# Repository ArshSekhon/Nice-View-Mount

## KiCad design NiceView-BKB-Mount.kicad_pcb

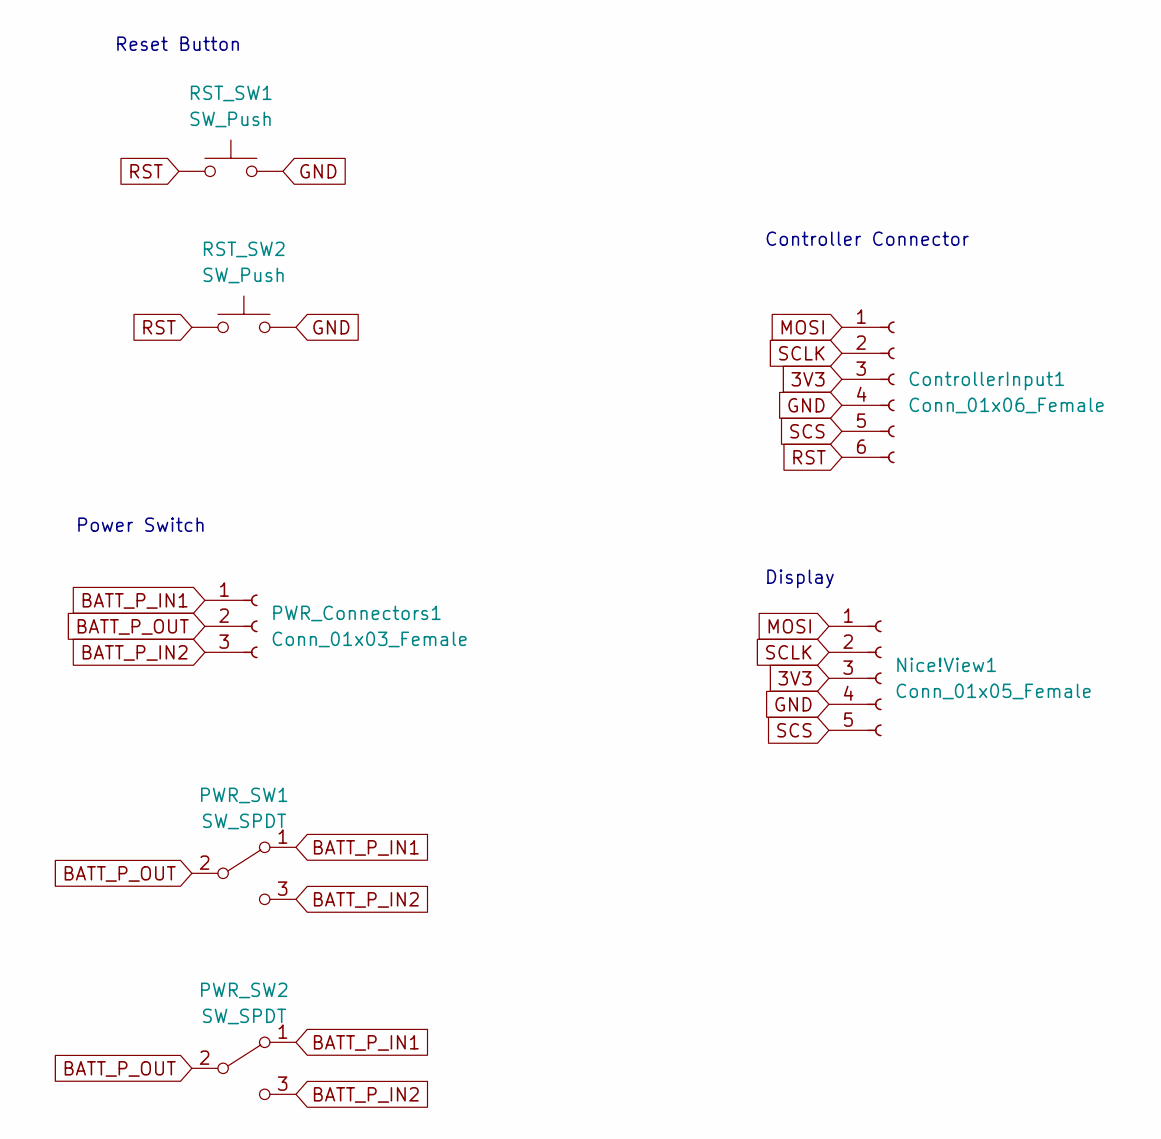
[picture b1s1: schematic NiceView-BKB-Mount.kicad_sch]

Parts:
ControllerInput1: Conn_01x06_Female; PinHeader_1x06_P2.54mm_Vertical
Nice!View1: Conn_01x05_Female; NiceView
PWR_Connectors1: Conn_01x03_Female; PinHeader_1x03_P2.54mm_Vertical
PWR_SW1, PWR_SW2: SW_SPDT; SW_SS12D07VG4
RST_SW1, RST_SW2: SW_Push; PushSwitch

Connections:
3V3: ControllerInput1.3, Nice!View1.3
BATT_P_IN1: PWR_Connectors1.1, PWR_SW1.1 (A), PWR_SW2.1 (A)
BATT_P_IN2: PWR_Connectors1.3, PWR_SW1.3 (C), PWR_SW2.3 (C)
BATT_P_OUT: PWR_Connectors1.2, PWR_SW1.2 (B), PWR_SW2.2 (B)
GND: ControllerInput1.4, Nice!View1.4, RST_SW1.2, RST_SW2.2
MOSI: ControllerInput1.1, Nice!View1.1
RST: ControllerInput1.6, RST_SW1.1, RST_SW2.1
SCLK: ControllerInput1.2, Nice!View1.2
SCS: ControllerInput1.5, Nice!View1.5

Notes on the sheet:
Reset Button
Controller Connector
Power Switch
Display

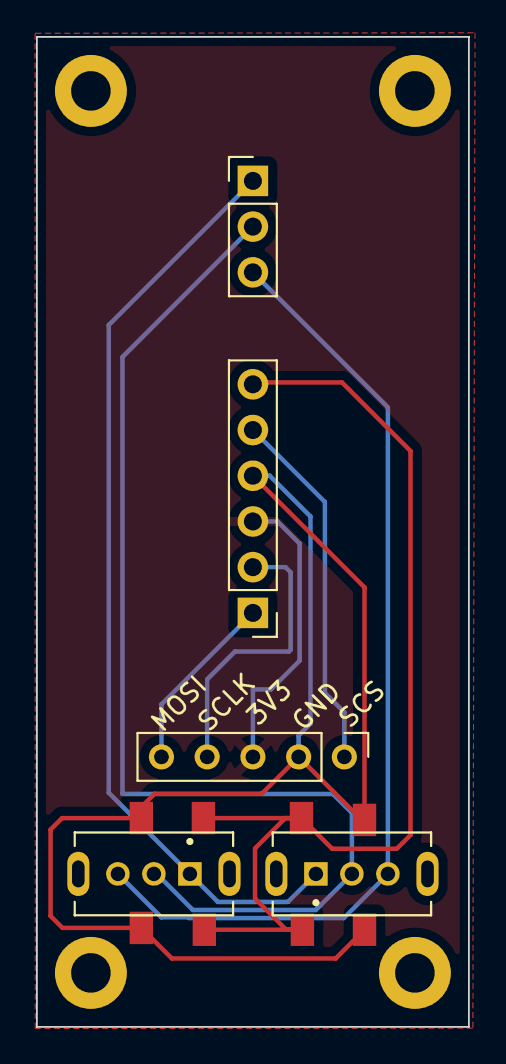
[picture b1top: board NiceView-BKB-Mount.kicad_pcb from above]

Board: 2 copper layers, 24.0 x 55.0 mm, 11 parts (0 on the bottom side), 9 nets.

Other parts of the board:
TH1, TH1#2, TH1#3, TH1#4: HOLE; M2_HOLE_PCB

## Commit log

2023-12-18 Intial Commit
